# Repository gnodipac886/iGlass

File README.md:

# iGlass

### [Powerpoint presentation](https://docs.google.com/presentation/d/1VVX9SU4g31F84sety2C6k8_4xhXHCecnRTAOGxrhhDY/edit?usp=sharing)
### [Undergraduate Thesis](https://drive.google.com/file/d/1tWfxlOyeyCUGNaeSUH1rKjghqD-MefPe/view?usp=sharing)

# Images
### iGlass v3 front

### iGlass v3 back

### iGlass v3 vs v2

### iGlass v2

### iGlass v2 pcb

### iGlass v1

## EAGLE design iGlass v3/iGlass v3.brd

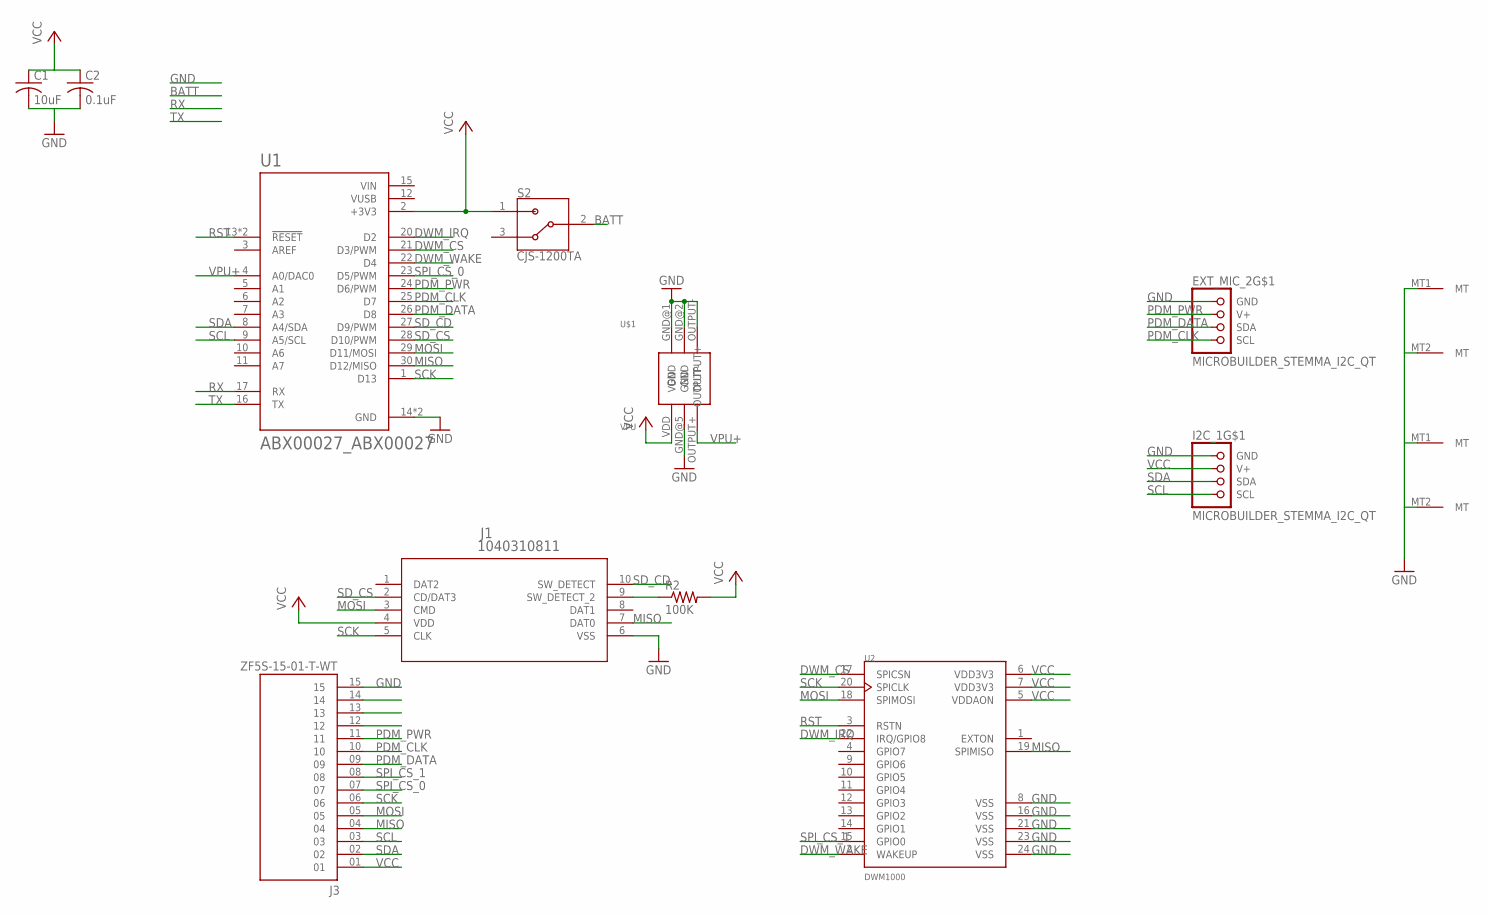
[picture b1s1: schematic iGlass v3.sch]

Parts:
C1: 10uF; C0805
C2: 0.1uF; C0805
EXT_MIC_2: MICROBUILDER_STEMMA_I2C_QT; MICROBUILDER_JST_SH4
I2C_1: MICROBUILDER_STEMMA_I2C_QT; MICROBUILDER_JST_SH4
J1: 1040310811; 104031-0811_MOL
J3: ZF5S-15-01-T-WT; SAMTEC_ZF5S-15-01-T-WT
R2: 100K; R0805
S2: CJS-1200TA; SW_CJS-1200TA
U1: ABX00027_ABX00027; ABX00027_MODULE_ABX00027
U2: DWM1000; XCVR_DWM1000
U$1: VPU

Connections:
BATT: S2.2
DWM_CS: U1.21 (D3/PWM), U2.17 (SPICSN)
DWM_IRQ: U1.20 (D2), U2.22 (IRQ/GPIO8)
DWM_WAKE: U1.22 (D4), U2.2 (WAKEUP)
GND: C1.2, C2.2, EXT_MIC_2.1 (GND), EXT_MIC_2.MT1 (MT), EXT_MIC_2.MT2 (MT), I2C_1.1 (GND), I2C_1.MT1 (MT), I2C_1.MT2 (MT), J1.6 (VSS), J3.14, J3.15, U1.14 (GND), U1.19 (GND), U2.8 (VSS), U2.16 (VSS), U2.21 (VSS), U2.23 (VSS), U2.24 (VSS), U$1.GND@1 (GND), U$1.GND@2 (GND), U$1.GND@5 (GND), U$1.OUTPUT-
MISO: J1.7 (DAT0), J3.04, U1.30 (D12/MISO), U2.19 (SPIMISO)
MOSI: J1.3 (CMD), J3.05, U1.29 (D11/MOSI), U2.18 (SPIMOSI)
unnamed: J1.9 (SW_DETECT_2), R2.1
PDM_CLK: EXT_MIC_2.4 (SCL), J3.10, U1.25 (D7)
PDM_DATA: EXT_MIC_2.3 (SDA), J3.09, U1.26 (D8)
PDM_PWR: EXT_MIC_2.2 (V+), J3.11, U1.24 (D6/PWM)
RST: U1.13 (!RESET), U1.18 (!RESET), U2.3 (RSTN)
RX: U1.17 (RX)
SCK: J1.5 (CLK), J3.06, U1.1 (D13), U2.20 (SPICLK)
SCL: I2C_1.4 (SCL), J3.03, U1.9 (A5/SCL)
SDA: I2C_1.3 (SDA), J3.02, U1.8 (A4/SDA)
SD_CD: J1.10 (SW_DETECT), U1.27 (D9/PWM)
SD_CS: J1.2 (CD/DAT3), U1.28 (D10/PWM)
SPI_CS_0: J3.07, U1.23 (D5/PWM)
SPI_CS_1: J3.08, U2.15 (GPIO0)
TX: U1.16 (TX)
VCC: C1.1, C2.1, I2C_1.2 (V+), J1.4 (VDD), J3.01, R2.2, S2.1, U1.2 (+3V3), U2.5 (VDDAON), U2.6 (VDD3V3), U2.7 (VDD3V3), U$1.VDD
VIN: U1.15 (VIN)
VPU+: U1.4 (A0/DAC0), U$1.OUTPUT+
VUSB: U1.12 (VUSB)

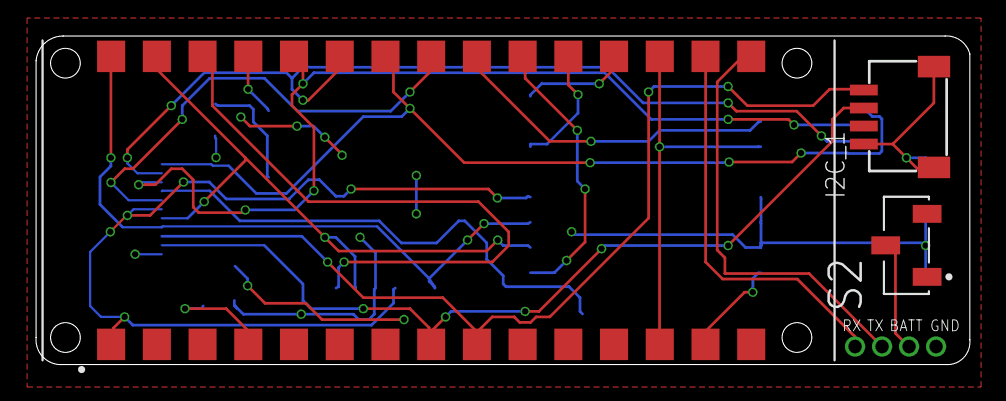
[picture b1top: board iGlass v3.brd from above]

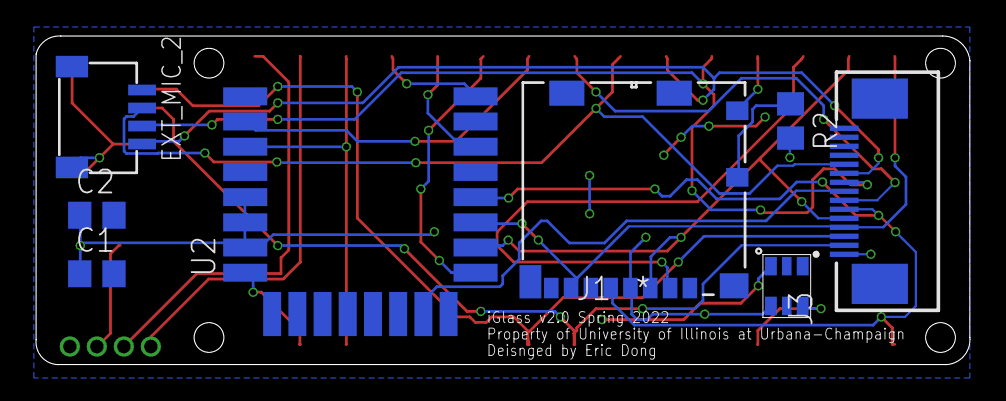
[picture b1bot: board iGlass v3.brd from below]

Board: 2 copper layers, 51.9 x 18.3 mm, 11 parts (8 on the bottom side), 20 nets.

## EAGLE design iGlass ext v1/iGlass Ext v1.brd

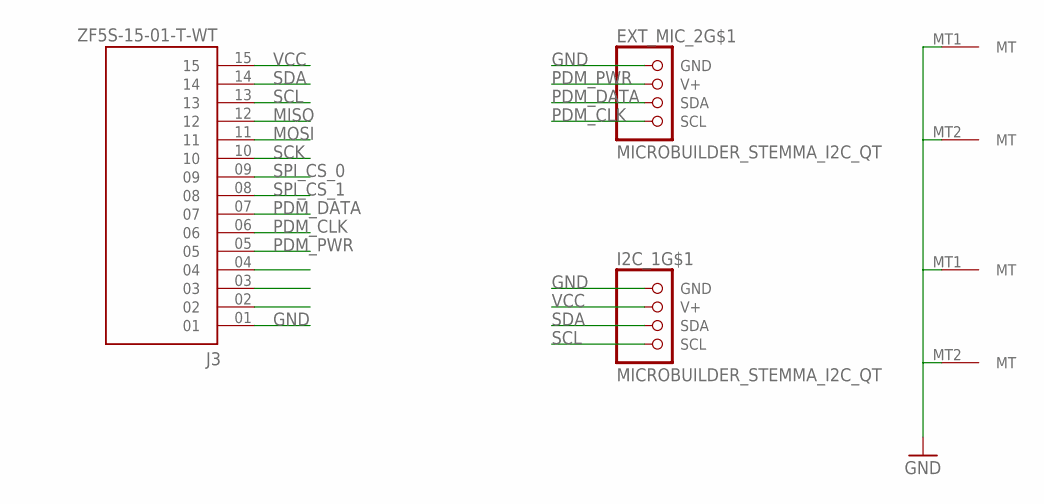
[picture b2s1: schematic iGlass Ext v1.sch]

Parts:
EXT_MIC_2: MICROBUILDER_STEMMA_I2C_QT; MICROBUILDER_JST_SH4
I2C_1: MICROBUILDER_STEMMA_I2C_QT; MICROBUILDER_JST_SH4
J3: ZF5S-15-01-T-WT; SAMTEC_ZF5S-15-01-T-WT

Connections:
GND: EXT_MIC_2.1 (GND), EXT_MIC_2.MT1 (MT), EXT_MIC_2.MT2 (MT), I2C_1.1 (GND), I2C_1.MT1 (MT), I2C_1.MT2 (MT), J3.01
MISO: J3.12
MOSI: J3.11
PDM_CLK: EXT_MIC_2.4 (SCL), J3.06
PDM_DATA: EXT_MIC_2.3 (SDA), J3.07
PDM_PWR: EXT_MIC_2.2 (V+), J3.05
SCK: J3.10
SCL: I2C_1.4 (SCL), J3.13
SDA: I2C_1.3 (SDA), J3.14
SPI_CS_0: J3.09
SPI_CS_1: J3.08
VCC: I2C_1.2 (V+), J3.15

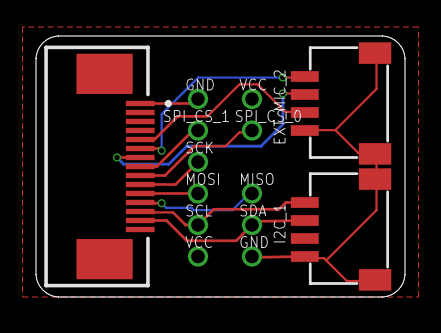
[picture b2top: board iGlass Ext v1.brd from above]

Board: 2 copper layers, 20.5 x 14.5 mm, 3 parts (0 on the bottom side), 7 nets.

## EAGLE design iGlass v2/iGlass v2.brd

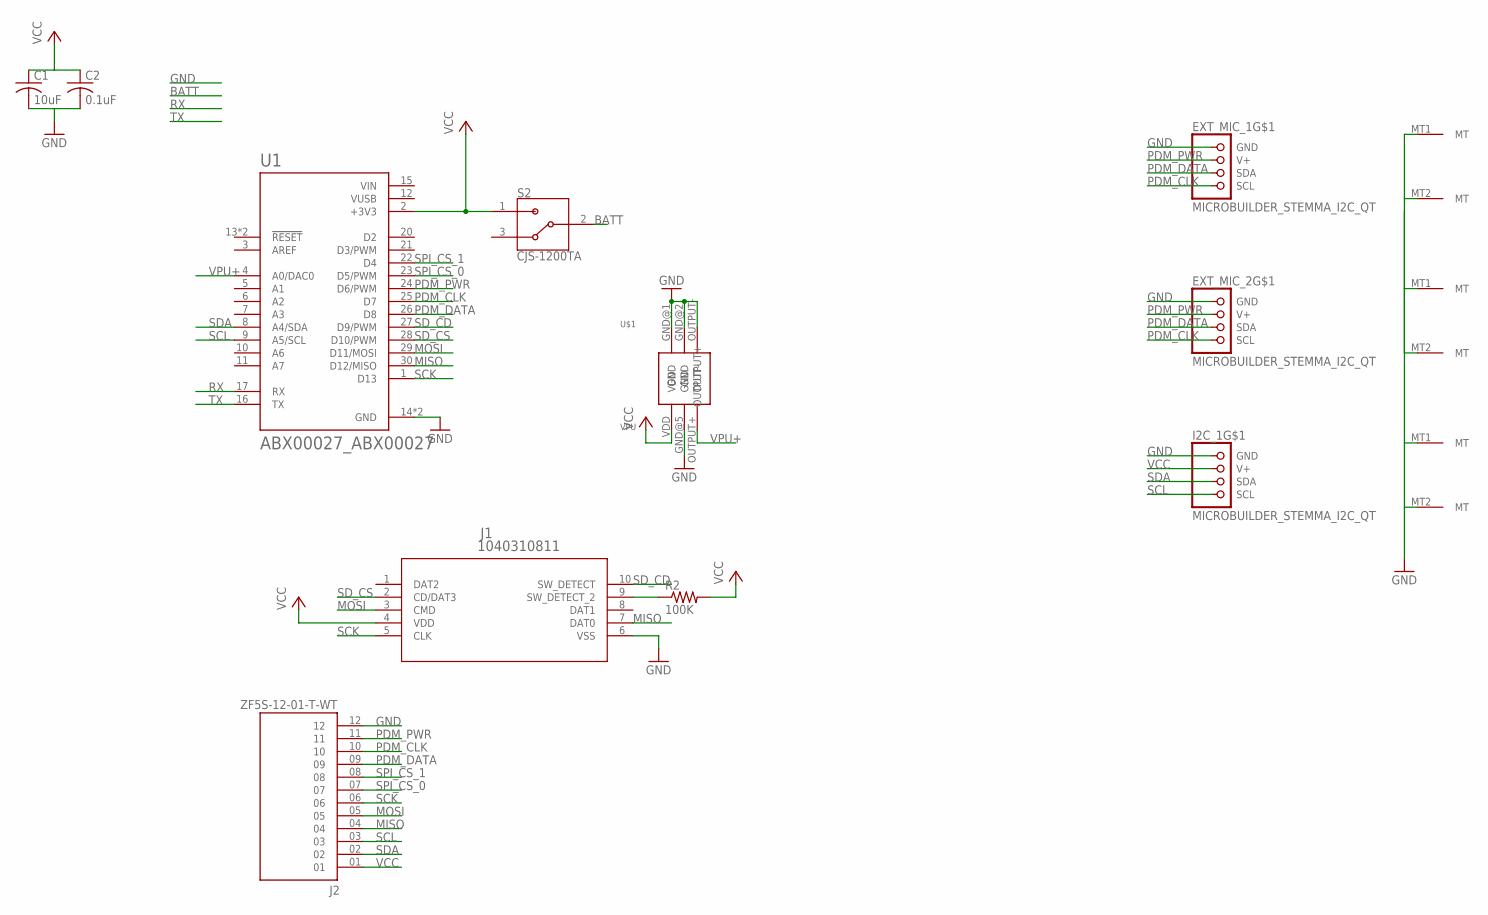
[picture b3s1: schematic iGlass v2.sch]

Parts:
C1: 10uF; C0805
C2: 0.1uF; C0805
EXT_MIC_1, EXT_MIC_2: MICROBUILDER_STEMMA_I2C_QT; MICROBUILDER_JST_SH4
I2C_1: MICROBUILDER_STEMMA_I2C_QT; MICROBUILDER_JST_SH4
J1: 1040310811; 104031-0811_MOL
J2: ZF5S-12-01-T-WT; SAMTEC_ZF5S-12-01-T-WT
R2: 100K; R0805
S2: CJS-1200TA; SW_CJS-1200TA
U1: ABX00027_ABX00027; ABX00027_MODULE_ABX00027
U$1: VPU

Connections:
BATT: S2.2
GND: C1.2, C2.2, EXT_MIC_1.1 (GND), EXT_MIC_1.MT1 (MT), EXT_MIC_1.MT2 (MT), EXT_MIC_2.1 (GND), EXT_MIC_2.MT1 (MT), EXT_MIC_2.MT2 (MT), I2C_1.1 (GND), I2C_1.MT1 (MT), I2C_1.MT2 (MT), J1.6 (VSS), J2.12, U1.14 (GND), U1.19 (GND), U$1.GND@1 (GND), U$1.GND@2 (GND), U$1.GND@5 (GND), U$1.OUTPUT-
MISO: J1.7 (DAT0), J2.04, U1.30 (D12/MISO)
MOSI: J1.3 (CMD), J2.05, U1.29 (D11/MOSI)
unnamed: J1.9 (SW_DETECT_2), R2.1
PDM_CLK: EXT_MIC_1.4 (SCL), EXT_MIC_2.4 (SCL), J2.10, U1.25 (D7)
PDM_DATA: EXT_MIC_1.3 (SDA), EXT_MIC_2.3 (SDA), J2.09, U1.26 (D8)
PDM_PWR: EXT_MIC_1.2 (V+), EXT_MIC_2.2 (V+), J2.11, U1.24 (D6/PWM)
RX: U1.17 (RX)
SCK: J1.5 (CLK), J2.06, U1.1 (D13)
SCL: I2C_1.4 (SCL), J2.03, U1.9 (A5/SCL)
SDA: I2C_1.3 (SDA), J2.02, U1.8 (A4/SDA)
SD_CD: J1.10 (SW_DETECT), U1.27 (D9/PWM)
SD_CS: J1.2 (CD/DAT3), U1.28 (D10/PWM)
SPI_CS_0: J2.07, U1.23 (D5/PWM)
SPI_CS_1: J2.08, U1.22 (D4)
TX: U1.16 (TX)
VCC: C1.1, C2.1, I2C_1.2 (V+), J1.4 (VDD), J2.01, R2.2, S2.1, U1.2 (+3V3), U$1.VDD
VIN: U1.15 (VIN)
VPU+: U1.4 (A0/DAC0), U$1.OUTPUT+
VUSB: U1.12 (VUSB)

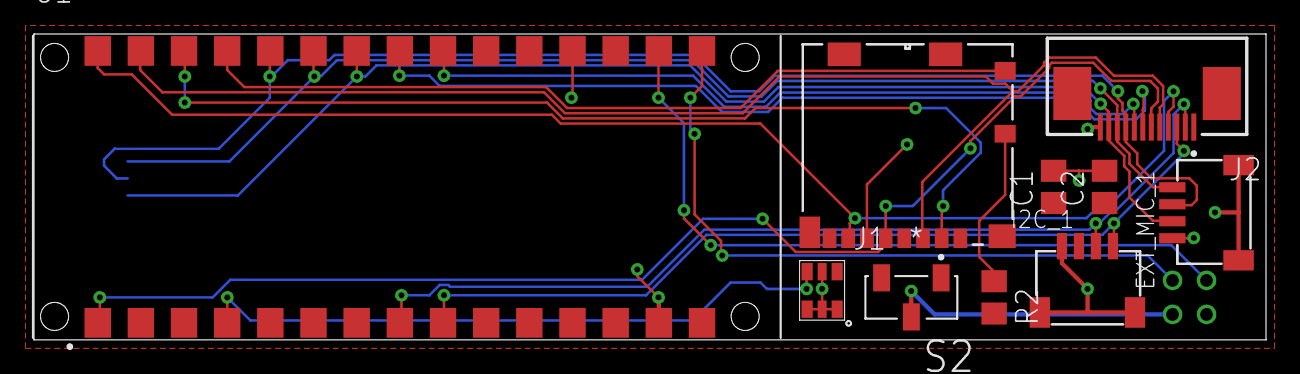
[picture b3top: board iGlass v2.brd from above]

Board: 2 copper layers, 72.5 x 18.0 mm, 11 parts (1 on the bottom side), 16 nets.

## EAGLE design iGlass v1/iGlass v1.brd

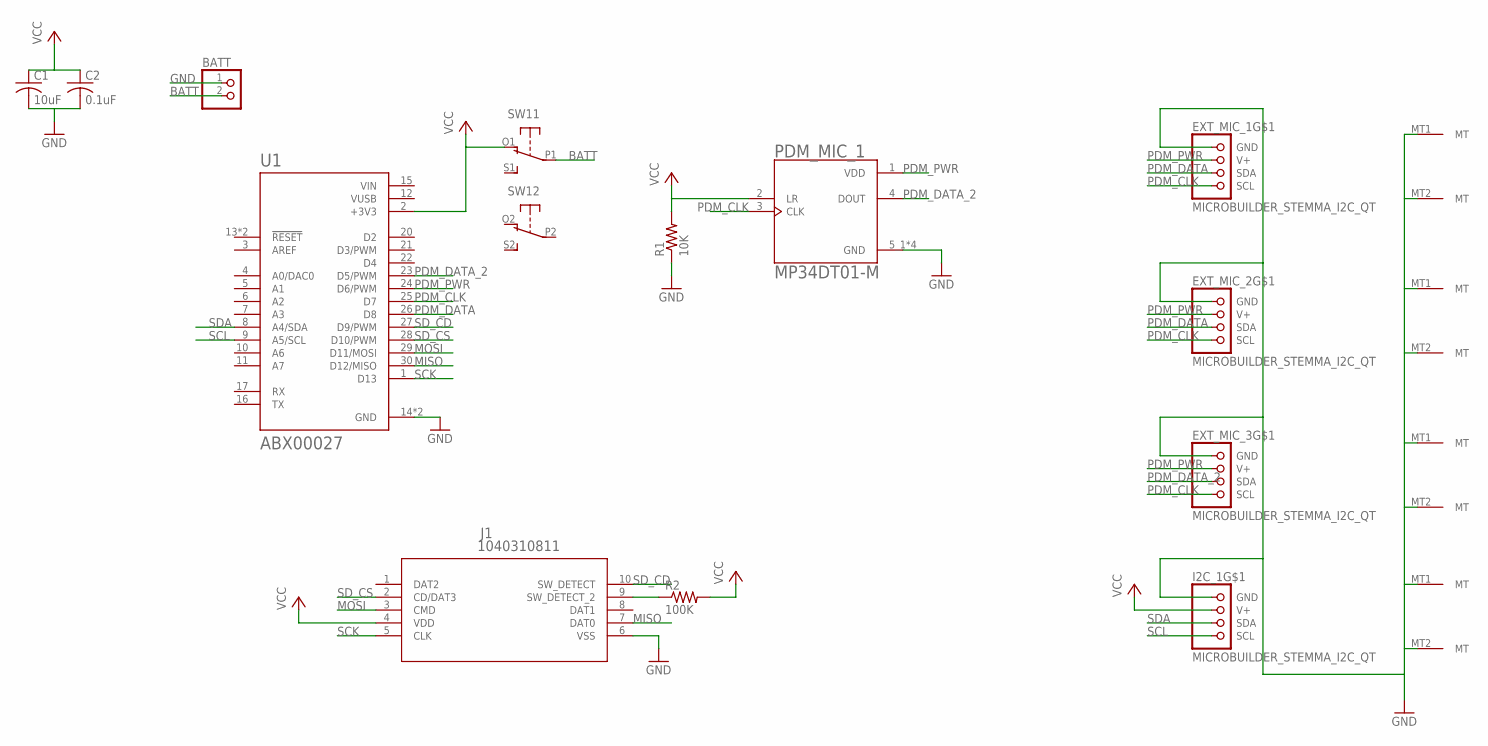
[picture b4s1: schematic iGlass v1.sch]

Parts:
BATT: CON_JST_PH_2PIN; JSTPH2
C1: 10uF; C0805
C2: 0.1uF; C0805
EXT_MIC_1, EXT_MIC_2, EXT_MIC_3: MICROBUILDER_STEMMA_I2C_QT; MICROBUILDER_JST_SH4
I2C_1: MICROBUILDER_STEMMA_I2C_QT; MICROBUILDER_JST_SH4
J1: 1040310811; 104031-0811_MOL
PDM_MIC_1: MP34DT01-M; MIC_MP34DT01-M
R1: 10K; R0805
R2: 100K; R0805
SW1: DPDT-EG1390; EG1390
U1: ABX00027; MODULE_ABX00027

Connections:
BATT: BATT.2, SW1.P1
GND: BATT.1, C1.2, C2.2, EXT_MIC_1.1 (GND), EXT_MIC_1.MT1 (MT), EXT_MIC_1.MT2 (MT), EXT_MIC_2.1 (GND), EXT_MIC_2.MT1 (MT), EXT_MIC_2.MT2 (MT), EXT_MIC_3.1 (GND), EXT_MIC_3.MT1 (MT), EXT_MIC_3.MT2 (MT), I2C_1.1 (GND), I2C_1.MT1 (MT), I2C_1.MT2 (MT), J1.6 (VSS), PDM_MIC_1.5_1 (GND), PDM_MIC_1.5_2 (GND), PDM_MIC_1.5_3 (GND), PDM_MIC_1.5_4 (GND), R1.1, U1.14 (GND), U1.19 (GND)
MISO: J1.7 (DAT0), U1.30 (D12/MISO)
MOSI: J1.3 (CMD), U1.29 (D11/MOSI)
unnamed: J1.9 (SW_DETECT_2), R2.1
PDM_CLK: EXT_MIC_1.4 (SCL), EXT_MIC_2.4 (SCL), EXT_MIC_3.4 (SCL), PDM_MIC_1.3 (CLK), U1.25 (D7)
PDM_DATA: EXT_MIC_1.3 (SDA), EXT_MIC_2.3 (SDA), U1.26 (D8)
PDM_DATA_2: EXT_MIC_3.3 (SDA), PDM_MIC_1.4 (DOUT), U1.23 (D5/PWM)
PDM_PWR: EXT_MIC_1.2 (V+), EXT_MIC_2.2 (V+), EXT_MIC_3.2 (V+), PDM_MIC_1.1 (VDD), U1.24 (D6/PWM)
SCK: J1.5 (CLK), U1.1 (D13)
SCL: I2C_1.4 (SCL), U1.9 (A5/SCL)
SDA: I2C_1.3 (SDA), U1.8 (A4/SDA)
SD_CD: J1.10 (SW_DETECT), U1.27 (D9/PWM)
SD_CS: J1.2 (CD/DAT3), U1.28 (D10/PWM)
VCC: C1.1, C2.1, I2C_1.2 (V+), J1.4 (VDD), PDM_MIC_1.2 (LR), R1.2, R2.2, SW1.O1 (O), U1.2 (+3V3)
VIN: U1.15 (VIN)
VUSB: U1.12 (VUSB)

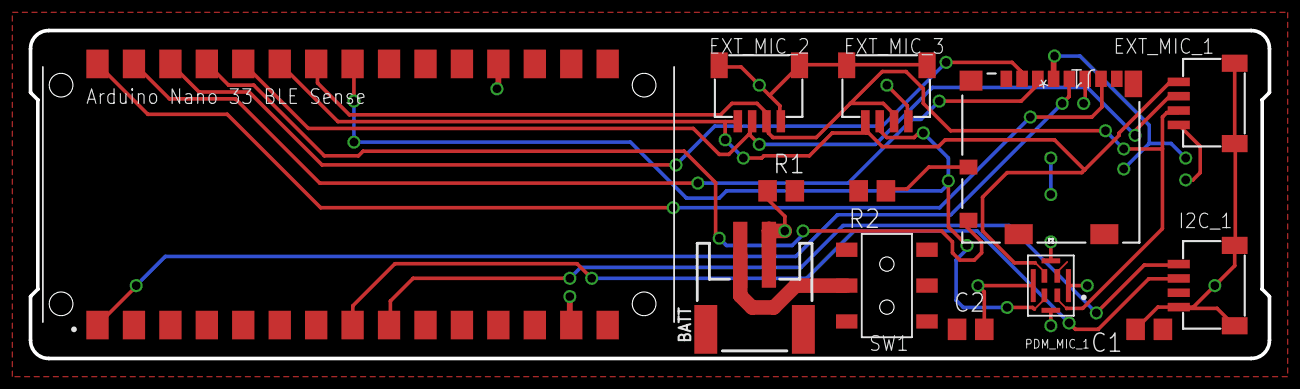
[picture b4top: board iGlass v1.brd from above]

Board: 2 copper layers, 86.4 x 22.9 mm, 13 parts (0 on the bottom side), 15 nets.

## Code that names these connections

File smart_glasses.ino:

#include <PDM.h>
#include "SdFat.h"
#include "sdios.h"
#include <Time.h>

#define PDM_BUF_SIZE 1024 * 16
#define IMU_BUF_SIZE 1024 * 9

#define DEBUG 0

#ifndef SDCARD_SS_PIN
const uint8_t SD_CS_PIN = SS;
#else  // SDCARD_SS_PIN
// Assume built-in SD is used.
const uint8_t SD_CS_PIN = SDCARD_SS_PIN;
#endif  // SDCARD_SS_PIN

// Try max SPI clock for an SD. Reduce SPI_CLOCK if errors occur.
#define SPI_CLOCK SD_SCK_MHZ(50)

// Try to select the best SD card configuration.
#if HAS_SDIO_CLASS
#define SD_CONFIG SdioConfig(FIFO_SDIO)
#elif ENABLE_DEDICATED_SPI
#define SD_CONFIG SdSpiConfig(SD_CS_PIN, DEDICATED_SPI, SPI_CLOCK)
#else  // HAS_SDIO_CLASS
#define SD_CONFIG SdSpiConfig(SD_CS_PIN, SHARED_SPI, SPI_CLOCK)
#endif  // HAS_SDIO_CLASSs


// IR Commands
#define GES_WRITE_SD 		    2     	//F
#define GES_STOP_WRITE_SD 		1     	//B
#define GES_SLEEP 			    3     	//U
#define GES_WAKE 			    4     	//D
#define GES_BLE_START			12		//FB
#define GES_BLE_STOP			21		//BF

// Others
#define USING_SD				0
#define USING_BLE				1

/****************Global Variables***************/

// sd card variables
	int chip_select = D10;
	int chip_detect = D9;

	SdExFat SD;
	ExFile mic_file;
	ExFile imu_file;

	String mic_fname = "mic_data";
	String imu_fname = "imu_data";

	volatile int card_present = 0;


// pdm microphone variables
	PDMClass PDM(D8, D7, D6);
	PDMClass PDM2(PIN_PDM_DIN, PIN_PDM_CLK, PIN_PDM_PWR);

	int mic_prev_time, mic_flush_counter = 0;

	// default number of output channels
	static char channels = 2;

	// default PCM output frequency, 41667
	static int frequency = 41667;

	// Buffer to read samples into, each sample is 16-bits
	short mic_sampleBuffer[PDM_BUF_SIZE];
	int pdm_sample_size = sizeof(short);// mic_sampleBuffer[0]);
	volatile int mic_print_arr;

	// Number of audio samples read
	volatile int samplesRead;


// imu variables
	float ax, ay, az, wx, wy, wz, mx, my, mz;
	float imu_sampleBuffer[IMU_BUF_SIZE];
	int imu_buf_idx = 0;


// IR variables
	int IR_command_given = 0;
	int IR_command = -1;

// others
	volatile int setup_complete, int_mic, int_imu = 0;
  unsigned long rgb_timer;
 
//Flags
	char SD_WRITE_FLAG = 0;
	int mic_setup_flag, imu_setup_flag, sd_setup_flag, ble_setup_flag = 0;
/***********************************************/

void setup() {
	#if DEBUG
	if(!Serial){
		Serial.begin(115200);
		// while (!Serial);
	}
	#endif

  pinMode(LED_BUILTIN, OUTPUT);
// 	setup_rgb();
//   setup_ir();
	// setup_sd_card();
	// attachInterrupt(digitalPinToInterrupt(chip_detect), card_detect, CHANGE);
	setup_complete = 1;
	ble_start_handler();
}

void loop() {
  //IR_gesture_check();........................................................................................
	// if(card_present && setup_complete && IR_command_given){    
	// 	//update_IMU();
	// 	IR_command_given = 0;
	// 	//Process IR_commands
	// 	switch(IR_command) {
	// 		case GES_WRITE_SD:
	// 			write_sd_handler(); 
	// 			break;
			
	// 		case GES_STOP_WRITE_SD:
	// 			stop_write_sd_handler();
	// 			break;

	// 		case GES_WAKE:
	// 			wake_from_sleep_handler();
	// 			break;

	// 		case GES_SLEEP:
	// 			go_to_sleep_handler();
	// 			break;

	// 		case GES_BLE_START:
	// 			ble_start_handler();					//flag + update ble function
	// 			break;

	// 		case GES_BLE_STOP:
	// 			ble_end_handler();
	// 			break;

	// 		default:
	// 			break;
    // 	}
    //     IR_command = -1;
	// } else if(card_present && !setup_complete){
	// 	imu_file = SD.open(imu_fname, O_WRITE | O_CREAT);
	// 	setup_complete = 1;
    // 	delay(100);
	// } else {
	// 	//Serial.println("SD card not present");
	// 	//delay(250);
	// }

	// if (SD_WRITE_FLAG == 1) {
	// 	if(mic_file) {
	// 		save_mic_data();
	// 	} else {
	// 		#if DEBUG
	// 		Serial.println("error opening mic_data file");
	// 		#endif
	// 	}
	// 	if(imu_file) {
	// 		update_IMU(imu_sampleBuffer);
	// 	} else {
	// 		#if DEBUG
	// 		Serial.println("error opening imu_data file");
	// 		#endif
	// 	}
	// }

	if (ble_setup_flag == 1) {
    // Serial.println("updating ble!!");
		update_ble();
	}
	//rgb
	// if (SD_WRITE_FLAG == 1 || ble_setup_flag == 1) {
	// 	if (millis()- rgb_timer >= 40) {
	// 	update_rgb();
	// 	rgb_timer = millis();
	// 	}
	// }
}

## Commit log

2021-09-16 Revert "added IR stuff"
2021-09-16 add gesture branch
2021-09-17 updated IR logic added_ forgot to debug, check for ;
2021-09-17 started ble branch
2021-09-22 IR basic function finished
2021-09-24 in the middle of implementing gesture commands...needa debug
2021-09-25 fixed PDM with editing source delete *_channels, integrated gestures with the rest
2021-09-25 added ble files
2021-10-01 ble works, rgb needs some more work
2021-10-08 added debug macros
2021-10-08 added PCB files
2021-10-08 minor change to board
2021-10-13 Got gestures/led lights timed working
2021-10-15 imu streams via ble, mic iffy
2021-10-20 set solid mic fs
2021-10-20 increased speed by doing continuous mode and edit source code to return num data in FIFO
2021-10-22 add python files, can classify
2021-10-28 data points are now a single float (norm of acceleration vector)
2021-10-28 changed to accepting one data point for imu acceleration
2021-10-28 unfinished need to convert float stuff to 2-byte stuff
2021-10-29 changed back int_16 to float
2021-10-29 int_16 -> float
2021-11-04 add new iGlass refactored code
2021-11-11 unittesting works, ble class
2021-11-12 done with ble head tracking
2021-11-18 add initial custom libraries
2021-11-18 can send 6-degree imu data acc gyro
2021-11-23 vtable issue for polymorphism of iglass apis
2021-11-23 add library for arduino
2021-11-23 arduino library draft 1 created!
2021-11-23 still debugging library
2021-11-24 solved idx array dereferencing issue (changed to idx not idx ptr) and new issue with imu.read for MAG came up
2021-12-03 semi-solved magnetometer ble update
2022-02-01 fixed static buffer issue
2022-02-06 fix gyro always 0
2022-02-06 add support for burst read acc gyro
2022-02-06 all 3 sensors 3 axis working, should be 120hz
2022-02-28 iGlass_mic done, compiles, not tested
2022-03-05 unittest folder added, sd works, sd unittest works (but code needs to be organized)
2022-03-06 changed a small commented-out include to make sense
2022-03-07 initial push to library branch
2022-03-07 add mic.h to compile
2022-03-11 rgb working
2022-03-12 add lsm9ds1 files, remove test.h
2022-03-12 add submodules
2022-03-25 code with hardarei2c issue, ir added
2022-03-25 add back deleted libraries, no dep issues
2022-03-25 add back rgb
2022-04-03 change mic buffer to variable read size
2022-04-06 mic unittest update
2022-07-14 add images for README
2022-07-31 7/31 examples should work; not all examples are here; src files completed, but still needs organization
2022-09-12 updated imu; only sd works with updated imu so far; sd can be improved...
2022-10-04 add pcb v2, v3
2022-10-04 imu code organization updated; imu unittest indicates that gyro's fifo buffer somehow fills up later than acc's fifo buffer does (not supposed to happen since they have the same ODR)
2022-10-04 sd code updated; when running the ino files, sd init fails when i press the reset button, once in a while, but should be fine (i hope)
2022-10-04 updated along with sd, imu, and mic files
2022-10-04 updated mic code
2022-10-05 just learned about callback functions, edited the function header for onPDM data

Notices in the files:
parts and their libraries:
micro_sd_slot: COPYRIGHT: Copyright (C) 2021 Ultra Librarian. All rights reserved.
